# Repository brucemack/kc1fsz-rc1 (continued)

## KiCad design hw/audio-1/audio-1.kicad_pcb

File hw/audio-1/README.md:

This is an early version which is no longer being used.

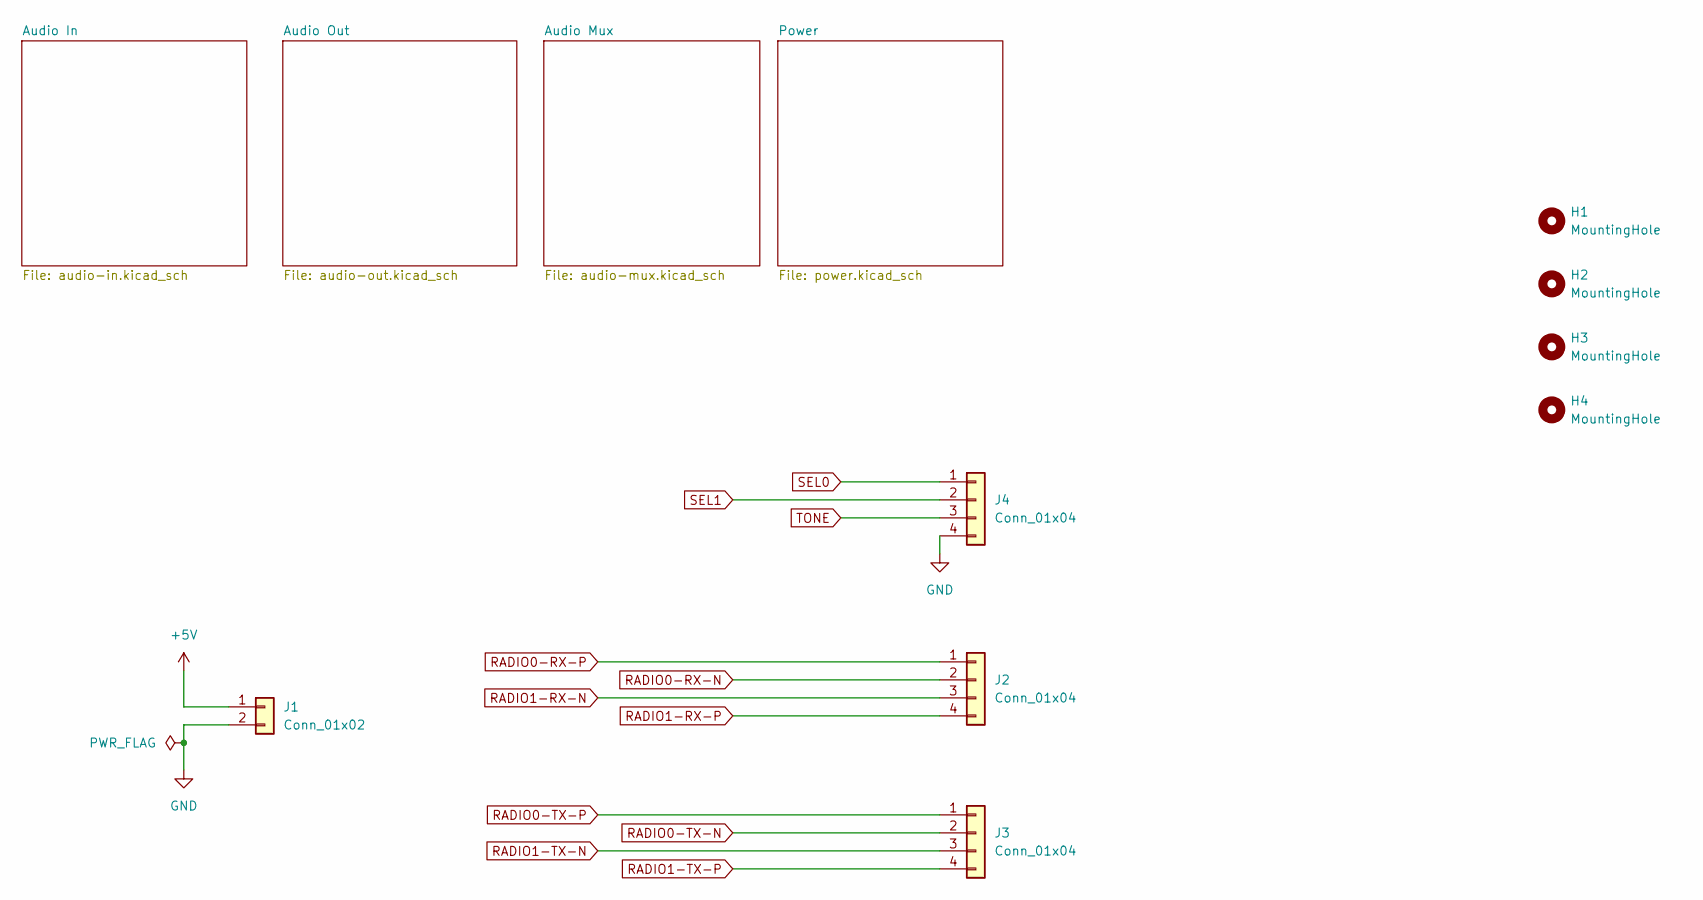
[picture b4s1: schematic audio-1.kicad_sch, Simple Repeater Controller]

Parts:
H1, H2, H3, H4: MountingHole; MountingHole_3.5mm
J1: Conn_01x02; PinHeader_1x02_P2.54mm_Vertical
J2, J3, J4: Conn_01x04; PinHeader_1x04_P2.54mm_Vertical

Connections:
+5V: J1.1; also elsewhere on the board
GND: J1.2, J4.4; also elsewhere on the board
RADIO0-RX-N: J2.2; also elsewhere on the board
RADIO0-RX-P: J2.1; also elsewhere on the board
RADIO0-TX-N: J3.2; also elsewhere on the board
RADIO0-TX-P: J3.1; also elsewhere on the board
RADIO1-RX-N: J2.3; also elsewhere on the board
RADIO1-RX-P: J2.4; also elsewhere on the board
RADIO1-TX-N: J3.3; also elsewhere on the board
RADIO1-TX-P: J3.4; also elsewhere on the board
SEL0: J4.1; also elsewhere on the board
SEL1: J4.2; also elsewhere on the board
TONE: J4.3; also elsewhere on the board

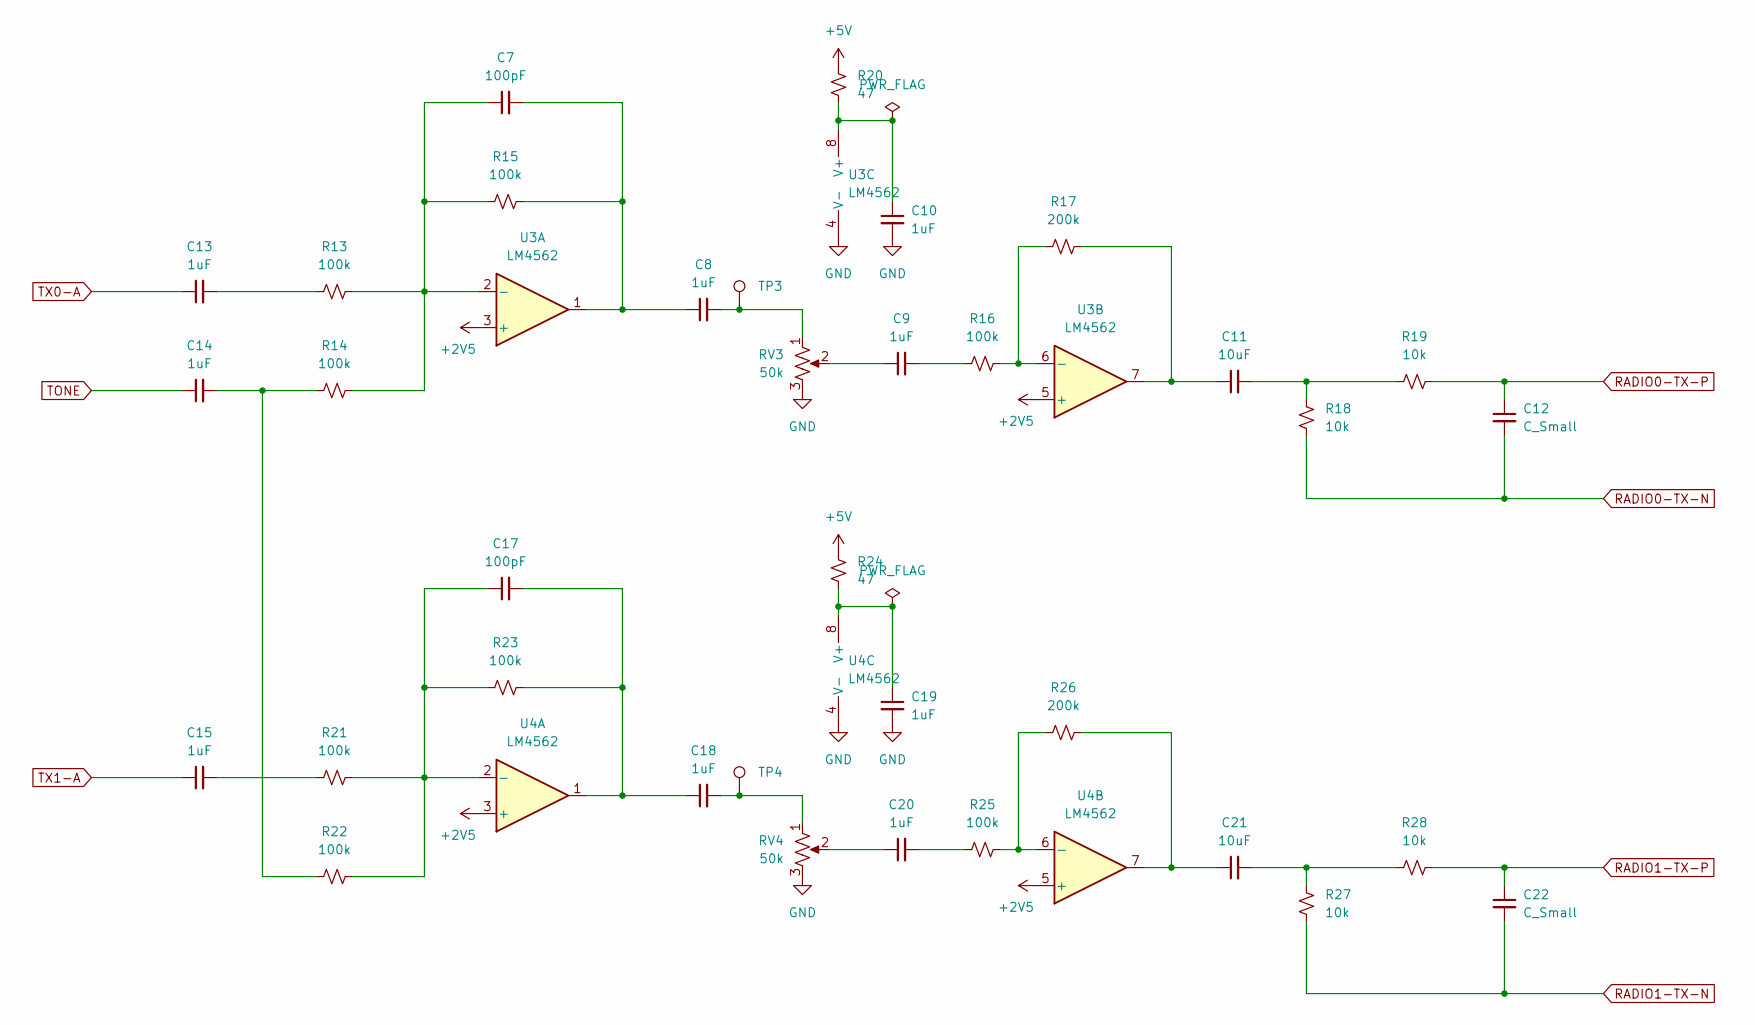
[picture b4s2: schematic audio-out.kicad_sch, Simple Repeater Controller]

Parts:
C7, C17: 100pF; C_0805_2012Metric_Pad1.18x1.45mm_HandSolder
C8, C9, C10, C13, C14, C15, C18, C19, C20: 1uF; C_0805_2012Metric_Pad1.18x1.45mm_HandSolder
C11, C21: 10uF; C_0805_2012Metric_Pad1.18x1.45mm_HandSolder
C12, C22: C_Small; C_0805_2012Metric_Pad1.18x1.45mm_HandSolder
R13, R14, R15, R16, R21, R22, R23, R25: 100k; R_0805_2012Metric_Pad1.20x1.40mm_HandSolder
R17, R26: 200k; R_0805_2012Metric_Pad1.20x1.40mm_HandSolder
R18, R19, R27, R28: 10k; R_0805_2012Metric_Pad1.20x1.40mm_HandSolder
R20, R24: 47; R_0805_2012Metric_Pad1.20x1.40mm_HandSolder
RV3, RV4: 50k; POT_3362P
TP3, TP4: TestPoint; TestPoint_Pad_3.0x3.0mm
U3, U4: LM4562; SOIC-8_3.9x4.9mm_P1.27mm

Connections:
+2V5: U3.3 (+), U3.5 (+), U4.3 (+), U4.5 (+); also elsewhere on the board
+5V: R20.2, R24.2; also elsewhere on the board
GND: C10.2, C19.2, RV3.3, RV4.3, U3.4 (V-), U4.4 (V-); also elsewhere on the board
unnamed: C7.2, C8.1, R15.2, U3.1
unnamed: C8.2, RV3.1, TP3.1
unnamed: C9.1, RV3.2
unnamed: C9.2, R16.1
unnamed: C11.1, R17.2, U3.7
unnamed: C11.2, R18.1, R19.1
unnamed: C13.2, R13.1
unnamed: C14.2, R14.1, R22.1
unnamed: C15.2, R21.1
unnamed: C17.2, C18.1, R23.2, U4.1
unnamed: C18.2, RV4.1, TP4.1
unnamed: C20.1, RV4.2
unnamed: C20.2, R25.1
unnamed: C21.1, R26.2, U4.7
unnamed: C21.2, R27.1, R28.1
unnamed: C7.1, R13.2, R14.2, R15.1, U3.2 (-)
unnamed: R16.2, R17.1, U3.6 (-)
unnamed: C10.1, R20.1, U3.8 (V+)
unnamed: C17.1, R21.2, R22.2, R23.1, U4.2 (-)
unnamed: R25.2, R26.1, U4.6 (-)
unnamed: C19.1, R24.1, U4.8 (V+)
RADIO0-TX-N: C12.2, R18.2; also elsewhere on the board
RADIO0-TX-P: C12.1, R19.2; also elsewhere on the board
RADIO1-TX-N: C22.2, R27.2; also elsewhere on the board
RADIO1-TX-P: C22.1, R28.2; also elsewhere on the board
TONE: C14.1; also elsewhere on the board
TX0-A: C13.1; also elsewhere on the board
TX1-A: C15.1; also elsewhere on the board

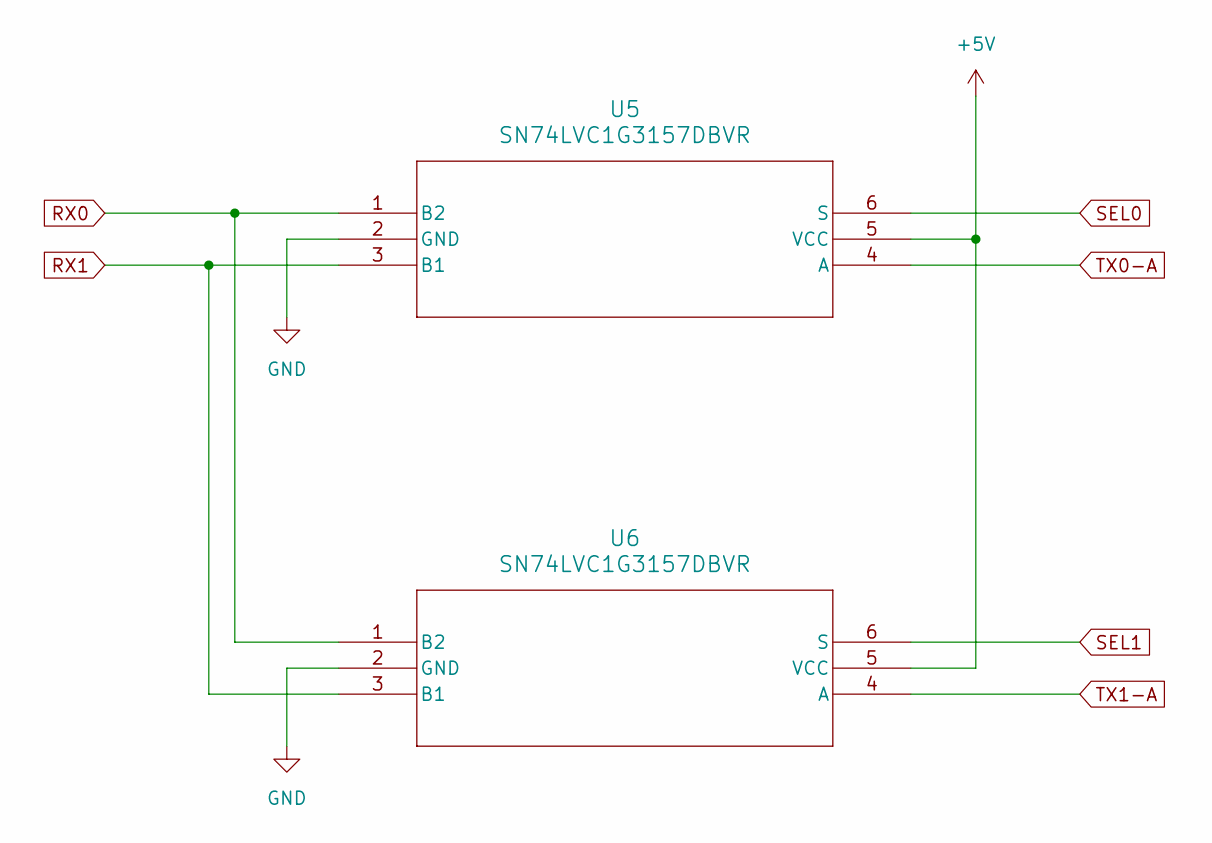
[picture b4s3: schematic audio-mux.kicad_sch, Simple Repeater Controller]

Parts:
U5, U6: SN74LVC1G3157DBVR; SOT-23-6_Handsoldering

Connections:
+5V: U5.5 (VCC), U6.5 (VCC); also elsewhere on the board
GND: U5.2 (GND), U6.2 (GND); also elsewhere on the board
RX0: U5.1 (B2), U6.1 (B2); also elsewhere on the board
RX1: U5.3 (B1), U6.3 (B1); also elsewhere on the board
SEL0: U5.6 (S); also elsewhere on the board
SEL1: U6.6 (S); also elsewhere on the board
TX0-A: U5.4 (A); also elsewhere on the board
TX1-A: U6.4 (A); also elsewhere on the board

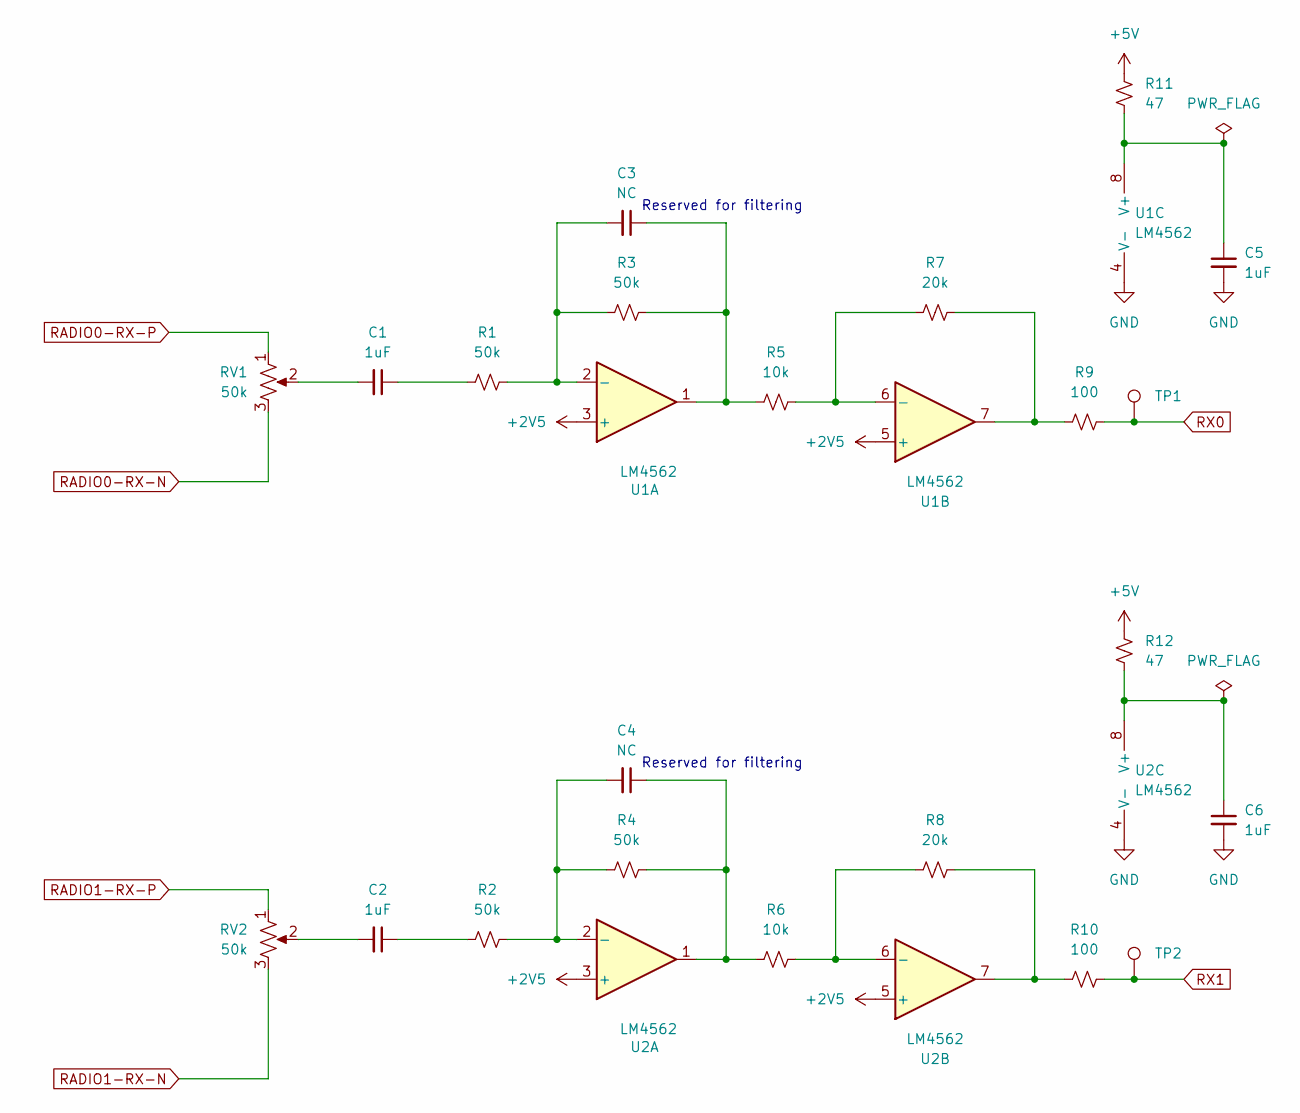
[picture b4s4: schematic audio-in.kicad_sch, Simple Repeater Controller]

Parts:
C1, C2, C5, C6: 1uF; C_0805_2012Metric_Pad1.18x1.45mm_HandSolder
C3, C4: NC; C_0805_2012Metric_Pad1.18x1.45mm_HandSolder
R1, R2, R3, R4: 50k; R_0805_2012Metric_Pad1.20x1.40mm_HandSolder
R5, R6: 10k; R_0805_2012Metric_Pad1.20x1.40mm_HandSolder
R7, R8: 20k; R_0805_2012Metric_Pad1.20x1.40mm_HandSolder
R9, R10: 100; R_0805_2012Metric_Pad1.20x1.40mm_HandSolder
R11, R12: 47; R_0805_2012Metric_Pad1.20x1.40mm_HandSolder
RV1, RV2: 50k; POT_3362P
TP1, TP2: TestPoint; TestPoint_Pad_3.0x3.0mm
U1, U2: LM4562; SOIC-8_3.9x4.9mm_P1.27mm

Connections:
+2V5: U1.3 (+), U1.5 (+), U2.3 (+), U2.5 (+); also elsewhere on the board
+5V: R11.1, R12.1; also elsewhere on the board
GND: C5.2, C6.2, U1.4 (V-), U2.4 (V-); also elsewhere on the board
unnamed: C1.1, R1.1
unnamed: C1.2, RV1.2
unnamed: C2.1, R2.1
unnamed: C2.2, RV2.2
unnamed: C3.1, R3.2, R5.1, U1.1
unnamed: C4.1, R4.2, R6.1, U2.1
unnamed: R7.2, R9.1, U1.7
unnamed: R8.2, R10.1, U2.7
unnamed: C3.2, R1.2, R3.1, U1.2 (-)
unnamed: R5.2, R7.1, U1.6 (-)
unnamed: C5.1, R11.2, U1.8 (V+)
unnamed: C4.2, R2.2, R4.1, U2.2 (-)
unnamed: R6.2, R8.1, U2.6 (-)
unnamed: C6.1, R12.2, U2.8 (V+)
RADIO0-RX-N: RV1.3; also elsewhere on the board
RADIO0-RX-P: RV1.1; also elsewhere on the board
RADIO1-RX-N: RV2.3; also elsewhere on the board
RADIO1-RX-P: RV2.1; also elsewhere on the board
RX0: R9.2, TP1.1; also elsewhere on the board
RX1: R10.2, TP2.1; also elsewhere on the board

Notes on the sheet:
Reserved for filtering

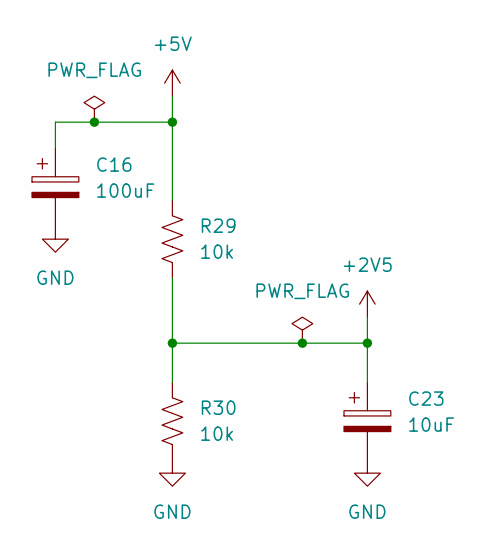
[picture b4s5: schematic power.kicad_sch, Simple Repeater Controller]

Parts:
C16: 100uF; CP_Radial_D5.0mm_P2.50mm
C23: 10uF; CP_Radial_D5.0mm_P2.50mm
R29, R30: 10k; R_0805_2012Metric_Pad1.20x1.40mm_HandSolder

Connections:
+2V5: C23.1, R29.2, R30.1; also elsewhere on the board
+5V: C16.1, R29.1; also elsewhere on the board
GND: C16.2, C23.2, R30.2; also elsewhere on the board

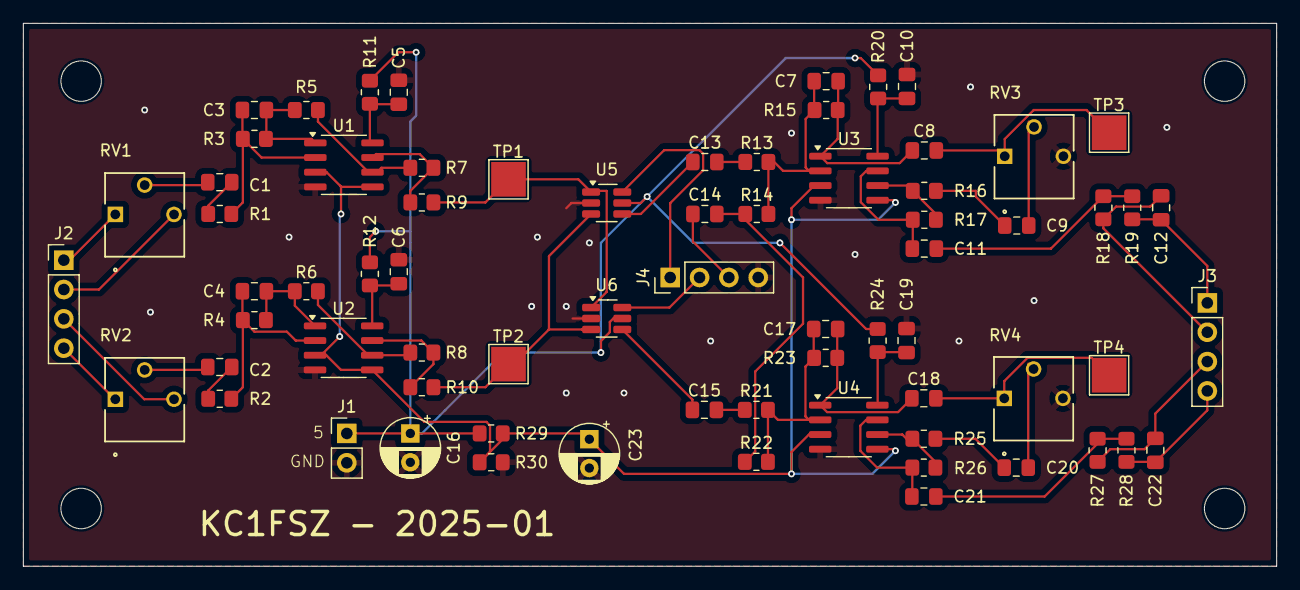
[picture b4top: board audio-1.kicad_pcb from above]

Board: 2 copper layers, 108.5 x 47.0 mm, 75 parts (0 on the bottom side), 53 nets.

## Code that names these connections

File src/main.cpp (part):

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// GPIO pin to be allocated to I2S SCK (output to CODEC)
const uint sck_pin = 4;
// Pin to be allocated to ADC ~RST
const uint adc_rst_pin = 5;
// Pin to be allocated to ADC I2S DIN (input from)
const uint adc_din_pin = 6;
// Pin to be allocated to DAC I2S DOUT 
const uint dac_dout_pin = 9;

#define LED_PIN (PICO_DEFAULT_LED_PIN)
#define R0_COS_PIN (14)
#define R0_CTCSS_PIN (13)
#define R0_PTT_PIN (12)
#define R1_COS_PIN (17)
#define R1_CTCSS_PIN (16)
#define R1_PTT_PIN (15)

#define WATCHDOG_INTERVAL_MS (2000)

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
    // TODO: REVIEW WHETHER THIS IS NEEDED
    // Reset the CODEC
    gpio_put(adc_rst_pin, 0);
    sleep_ms(100);
    gpio_put(adc_rst_pin, 1);
    sleep_ms(100);

    // ===== I2S SCK PIO Setup ===============================================
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    // power is supplied ..."
    //
    sleep_ms(100);
    gpio_put(adc_rst_pin, 0);
    sleep_ms(5);
    gpio_put(adc_rst_pin, 1);

    // Per PCM1804 datasheet page 18: 
    //
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    // clocks are being driven at the target frequency.

    sleep_ms(100);
    gpio_put(adc_rst_pin, 0);
    sleep_ms(100);
    gpio_put(adc_rst_pin, 1);
}

static int calc_rms_db(float* data, unsigned int dataSize, float maxValue) {
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    gpio_init(LED_PIN);
    gpio_set_dir(LED_PIN, GPIO_OUT);
    
    gpio_init(R0_COS_PIN);
    gpio_set_dir(R0_COS_PIN, GPIO_IN);
    gpio_init(R0_CTCSS_PIN);
    gpio_set_dir(R0_CTCSS_PIN, GPIO_IN);
    gpio_init(R0_PTT_PIN);
    gpio_set_dir(R0_PTT_PIN, GPIO_OUT);
    gpio_put(R0_PTT_PIN, 0);
    gpio_init(R1_COS_PIN);
    gpio_set_dir(R1_COS_PIN, GPIO_IN);
    gpio_init(R1_CTCSS_PIN);
    gpio_set_dir(R1_CTCSS_PIN, GPIO_IN);
    gpio_init(R1_PTT_PIN);
    gpio_set_dir(R1_PTT_PIN, GPIO_OUT);
    gpio_put(R1_PTT_PIN, 0);

    gpio_init(adc_rst_pin);
    gpio_set_dir(adc_rst_pin, GPIO_OUT);
    gpio_put(adc_rst_pin, 1);

    // Startup ID
    sleep_ms(500);
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    PicoPollTimer flashTimer;
    flashTimer.setIntervalUs(500 * 1000);

    StdTx tx0(clock, log, 0, R0_PTT_PIN, plSynth0);

    StdTx tx1(clock, log, 1, R1_PTT_PIN, plSynth1);

    StdRx rx0(clock, log, 0, R0_COS_PIN, R0_CTCSS_PIN, CourtesyToneGenerator::Type::FAST_UPCHIRP);

    StdRx rx1(clock, log, 1, R1_COS_PIN, R1_CTCSS_PIN, CourtesyToneGenerator::Type::FAST_DOWNCHIRP);

    TxControl txCtl0(clock, log, tx0, cwSynth0, audioSource0);
    TxControl txCtl1(clock, log, tx1, cwSynth1, audioSource1);
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
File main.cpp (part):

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
#define LED_PIN (PICO_DEFAULT_LED_PIN)
#define RADIO0_AUDIO_SEL_GPIO (4)
#define PTT0_GPIO (5)
#define COS0_GPIO (6)
#define RADIO1_AUDIO_SEL_GPIO (7)
#define PTT1_GPIO (8)
#define COS1_GPIO (9)
#define TONE_GPIO (10)

enum MasterState {
    RESET,
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// Each time the timer fires we advance forward to the next entry
// in the synth_table.
static bool synth_timer_isr(struct repeating_timer*) {
    uint pwm_slice = pwm_gpio_to_slice_num(TONE_GPIO);
    if (synth_enabled) {
        uint8_t v = synth_table[synth_ptr++];
        if (synth_ptr == synth_size)
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    gpio_set_dir(RADIO0_AUDIO_SEL_GPIO, GPIO_OUT);
    gpio_put(RADIO0_AUDIO_SEL_GPIO, 0);

    gpio_init(PTT0_GPIO);
    gpio_set_dir(PTT0_GPIO, GPIO_OUT);
    gpio_put(PTT0_GPIO, 0);

    gpio_init(COS0_GPIO);
    gpio_set_dir(COS0_GPIO, GPIO_IN);

    gpio_init(RADIO1_AUDIO_SEL_GPIO);
    gpio_set_dir(RADIO1_AUDIO_SEL_GPIO, GPIO_OUT);
    gpio_put(RADIO1_AUDIO_SEL_GPIO, 0);

    gpio_init(PTT1_GPIO);
    gpio_set_dir(PTT1_GPIO, GPIO_OUT);
    gpio_put(PTT1_GPIO, 0);

    gpio_init(COS1_GPIO);
    gpio_set_dir(COS1_GPIO, GPIO_IN);

    // Startup ID
    sleep_ms(500);
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    timeoutTimer.setIntervalUs(30 * 1000 * 1000);

    // Setup PWM test
    gpio_set_function(TONE_GPIO, GPIO_FUNC_PWM);
    uint pwm_slice = pwm_gpio_to_slice_num(TONE_GPIO);
    // Control the size of the loop (inclusive)
    pwm_set_wrap(pwm_slice, 255);
    // Running with no clock divisor, so the pulse frequency is 125,000,000 / 256 
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        if (c == 's') {
            printf("Status:\n");
            printf("  State %d\n", (int)state);
            printf("  COS0 %d\n", gpio_get(COS0_GPIO));
            printf("  COS1 %d\n", gpio_get(COS1_GPIO));
        }
        else if (c == 'r') {
            state = MasterState::RESET;
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        if (state == MasterState::RESET) {
            printf("Resetting ...\n");
            gpio_put(RADIO0_AUDIO_SEL_GPIO, 0);
            gpio_put(PTT0_GPIO, 0);
            gpio_put(RADIO1_AUDIO_SEL_GPIO, 1);
            gpio_put(PTT1_GPIO, 0);
            state = MasterState::IDLE;
        } 
        else if (state == MasterState::IDLE) {
            // Look for RADIO0 RX activity
            if (gpio_get(COS0_GPIO) == 0) {
                // Both radios transmitting radio 0 RX audio
                gpio_put(RADIO0_AUDIO_SEL_GPIO, 1);
                gpio_put(RADIO1_AUDIO_SEL_GPIO, 1);
                // Key radios
                gpio_put(PTT0_GPIO, 1);
                gpio_put(PTT1_GPIO, 1);
                // Indicator
                gpio_put(LED_PIN, 1);
                printf("Radio0 receiving\n");
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                state = MasterState::RADIO0_RX;
            }
            // Look for RADIO1 RX activity
            else if (gpio_get(COS1_GPIO) == 0) {
                // Both radios transmitting radio 1 RX audio
                gpio_put(RADIO0_AUDIO_SEL_GPIO, 0);
                gpio_put(RADIO1_AUDIO_SEL_GPIO, 0);
                // Key radios
                gpio_put(PTT0_GPIO, 1);
                gpio_put(PTT1_GPIO, 1);
                // Indication
                gpio_put(LED_PIN, 1);
                printf("Radio1 receiving\n");
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            // Look for timeout
            if (maxTxTimer.poll()) {
                // Unkey radios
                gpio_put(PTT0_GPIO, 0);
                gpio_put(PTT1_GPIO, 0);
                // Indication
                gpio_put(LED_PIN, 0);
                printf("Timeout 0\n");
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                gpio_put(RADIO1_AUDIO_SEL_GPIO, 0);
            }
            // Look for RADIO0 COS drop 
            else if (gpio_get(COS0_GPIO) == 1) {            
                if (cosDebounceTimer.poll()) {
                    // Unkey radios
                    gpio_put(PTT0_GPIO, 0);
                    gpio_put(PTT1_GPIO, 0);
                    // Indication
                    gpio_put(LED_PIN, 0);
                    printf("Radio0 stopped receiving\n");
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            // Look for timeout
            if (maxTxTimer.poll()) {
                // Unkey radios
                gpio_put(PTT0_GPIO, 0);
                gpio_put(PTT1_GPIO, 0);
                // Indication
                gpio_put(LED_PIN, 0);
                printf("Timeout 1\n");
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                gpio_put(RADIO1_AUDIO_SEL_GPIO, 0);
            }
            // Look for RADIO1 drop 
            else if (gpio_get(COS1_GPIO) == 1) {            
                if (cosDebounceTimer.poll()) {
                    // Unkey radios
                    gpio_put(PTT0_GPIO, 0);
                    gpio_put(PTT1_GPIO, 0);
                    // Indication
                    gpio_put(LED_PIN, 0);
                    printf("Radio1 stopped receiving\n");
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
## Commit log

2025-01-16 Version used to generage gerbers
2025-01-16 Uploaded to JLCPCB
2025-01-17 Control-1 sent to JLCPCB
2025-01-31 Docs improvements
2025-02-01 Basic state machine working
2025-02-01 Working on tone test
2025-02-03 Working on DTMF detection
2025-03-11 Docs
2025-03-11 Working
2025-03-11 Clean up
2025-03-12 Added timeout
2025-03-12 Build
2025-03-17 Working on 2
2025-03-17 Working on V2
2025-03-18 First draft of schematic
2025-03-18 Similations
2025-03-18 Working on simulation
2025-03-18 Simulations
2025-03-18 Adding changes suggested by Dan
2025-05-08 Ready to do layout on IF2 board
2025-05-09 Making progress on layout
2025-05-10 Workig on routing
2025-05-11 Progress on layout
2025-05-11 Layout passes DRC!!
2025-05-12 (Pre fab) Resolved warning with DB25 shell connections to ground
2025-05-12 New board
2025-05-12 (Pre fab) Added fill on bottom layer
2025-05-13 Digital board complete
2025-05-13 All boards ready
2025-05-13 Ready to send to fab
2025-05-15 Preparing for digital version
2025-05-15 Initial structure
2025-05-15 Working on structure
2025-05-15 Basic timeout structure is working
2025-05-15 Working on states
2025-05-15 Initial states working
2025-05-16 Working on improving state machine
2025-05-16 State machine improved
2025-05-16 Improvements to state machine
2025-05-16 Improved logging
2025-05-17 Created first QA test
2025-05-30 New files
2025-05-30 Adding HW integration
2025-05-30 Working on HW integration
2025-05-31 COS/PTT on radio 0 working
2025-05-31 Demonstraion working
2025-06-01 Documentation improvements, moved a OVP circuit
2025-06-16 Audio not working
2025-06-16 Getting a pure tone from the DAC
2025-06-16 CW ID is working
2025-06-16 Tones working
2025-06-18 PL encoding working
2025-06-18 Added ability to route audio from RX->TX. NOT TESTED YET
2025-06-18 Integrating second transmitter, refactoring PL generation
2025-06-18 Cleaned up compile errors - not tested yet
2025-06-19 Two TX PL tone is working
2025-06-19 Different courtesy tones for radio 0 and radio 1
2025-06-19 Repeating from radio 0 audio input successfully
2025-06-19 Added audio clip
2025-06-20 Testing voice ID
2025-06-20 Added diagnostic tone
2025-06-20 Adding VU meter
2025-06-21 Working on docs
2025-06-21 Working on levels
2025-06-22 Audio diagnostic testing, system working.
2025-06-22 Improved management of history buffers/RMS calculation. Now only storing 8 bits of output history
2025-06-22 Adding envelope to audio sources
2025-06-22 Changed to 32000 audio
2025-06-22 Updated audio file to 16K
2025-06-22 Integrated Dan's audio prompt
2025-06-22 Added watchdog
2025-06-22 Enabled watchdog timer
2025-06-23 Adding CTCSS
2025-06-23 Refactoring, introduced ui mode
2025-06-23 New generalized morse generator
2025-06-23 Configuration strrrrrrrructure
2025-06-24 Working on users manual
2025-06-24 Updating schematics, create new mini-board for radio interface
2025-06-25 Major work on configuraitons, not tested
2025-06-25 Configuration work - compiles again
2025-06-25 Refactored shell command and show config
2025-06-26 Added configuration defaults
2025-06-26 Working on config
2025-06-26 NOT TESTED Finished the config show code
2025-06-27 NOT TESTED, refactored RX COS/Tone logic. Now supporting polarity and debounce
2025-06-27 New COS/TONE pin mechanism, testing in process
2025-06-27 Gain config, etc
2025-06-27 Working on test tone
2025-06-27 Testing in process
2025-06-28 Moving east
2025-07-04 CTCSS detection
2025-07-06 Working on audio core, with test harness
2025-07-06 Noise squelch HPF working
2025-07-07 Working on test clips
2025-07-07 Working on decimation
2025-07-08 Decimation to 16k is working
2025-07-08 Working on noise squelch
2025-07-08 Resampled files
2025-07-09 CTCSS decoder working
2025-07-09 CTCSS decode
2025-07-10 Improvements to CTCSS
2025-07-10 Improvements to CTCSS filering/detection
2025-07-10 Output filter
2025-07-11 Interpolation work
2025-07-11 Added CTCSS encode
2025-07-11 Working on CTCSS encode
2025-07-11 Working on CTCSS
2025-07-11 Audio delay
2025-07-13 Added clips used for testing
2025-07-16 Added audio spectrum test
2025-07-23 Removed obsolete software, code migrated to different repo
2025-07-23 AGC docs
2025-07-24 Rig interface
2025-07-24 DTMF stuff
2025-07-25 DTMF docs
